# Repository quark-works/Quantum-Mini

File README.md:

# Quantum MINI

rp2040 based controller with a SPDT switch for changing memory bank.

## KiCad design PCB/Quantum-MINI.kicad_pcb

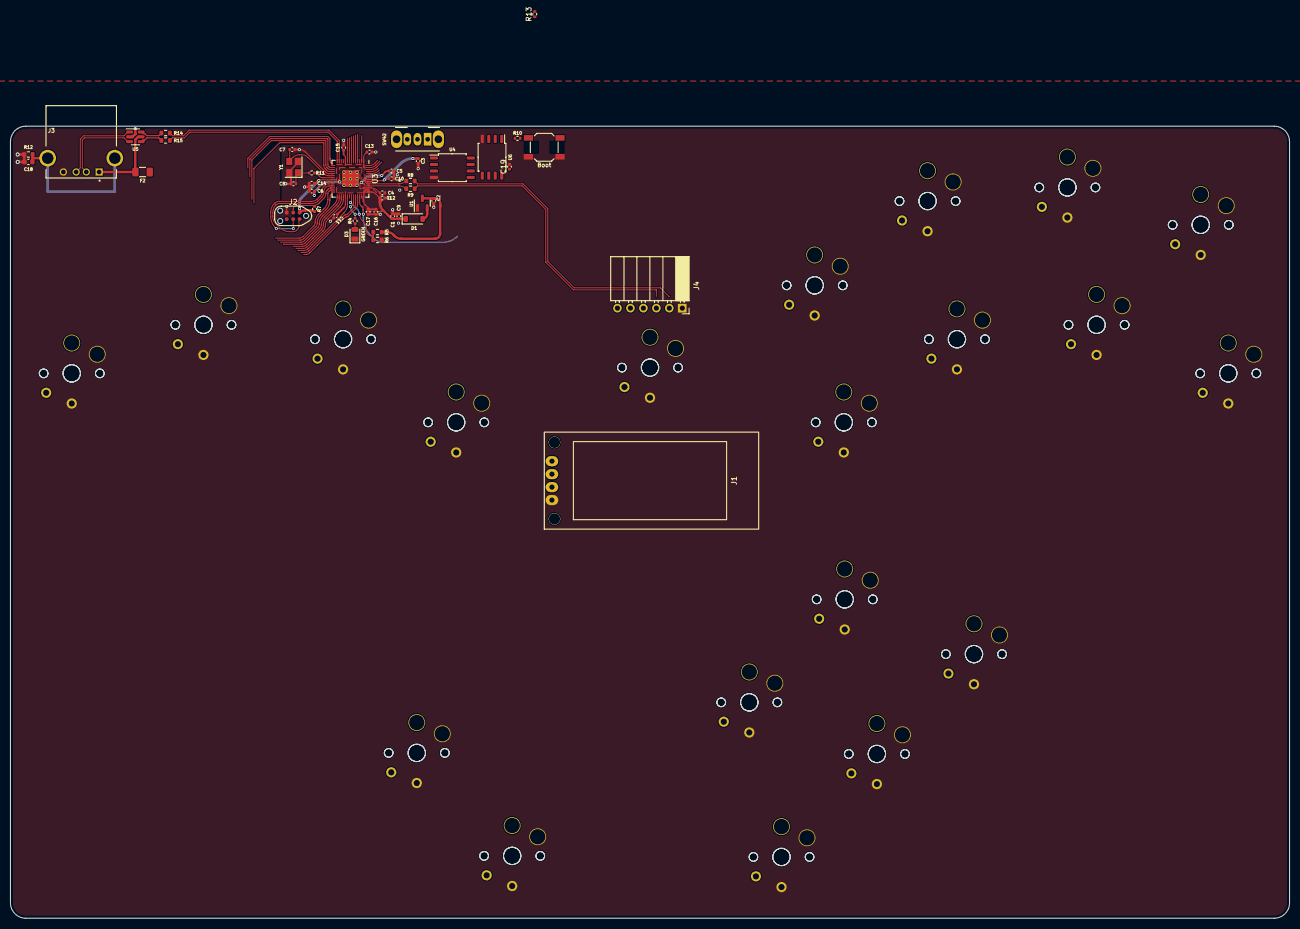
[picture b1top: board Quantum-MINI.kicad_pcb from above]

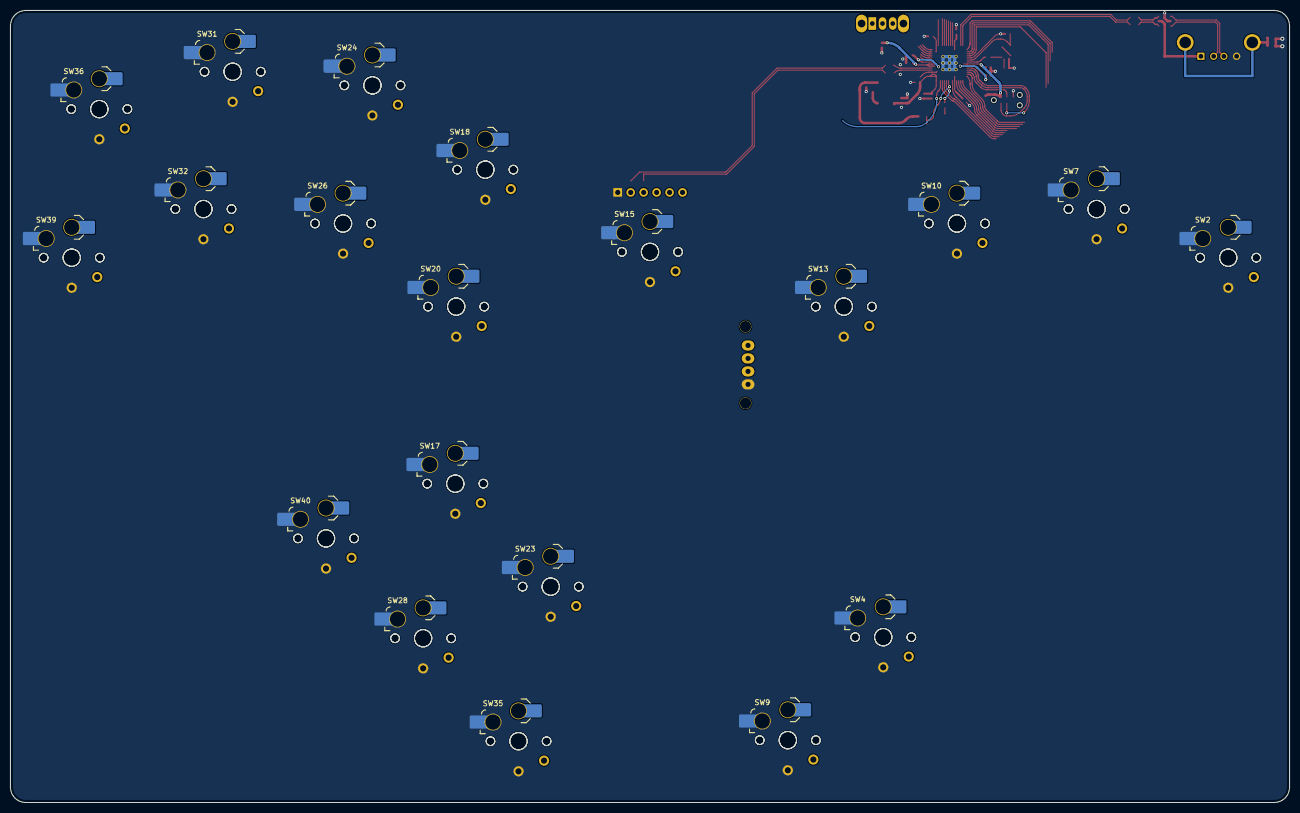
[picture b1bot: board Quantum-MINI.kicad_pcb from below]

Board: 2 copper layers, 250.6 x 155.2 mm, 86 parts (20 on the bottom side), 57 nets.

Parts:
C1, C2, C4, C10: 1uF; C_0402_1005Metric
C3, C5, C6, C11, C12, C13, C14, C15, C16, C17, C19: 100nF; C_0402_1005Metric
C7, C8: 22pF; C_0402_1005Metric
C9: 10uF; C_0402_1005Metric
C18: 4.7uf; C_0603_1608Metric
D1: Schottky Diode; D_SOD-123
D3: GREEN; LED_0805_2012Metric
F2: 500 mA; Fuse_1206_3216Metric
J1: Conn_01x04; SH1107
J2: JTAG_TC2030; CON_TC2030_outlined
J3: USB_A; GCT_USB1130-15-A_REVA
J4: Conn_01x06; PinSocket_1x06_P2.54mm_Horizontal
R4, R7, R10, R13: 10k; R_0402_1005Metric
R5: 5.6k; R_0603_1608Metric
R6: 10k; R_0603_1608Metric
R8, R9: 27; R_0603_1608Metric
R11: 1k; R_0402_1005Metric
R12: 1M; R_0603_1608Metric
R14, R15: 22; R_0603_1608Metric
SW1: Boot; SW_SPST_SKQG_WithStem
SW2, SW4, SW7, SW9, SW10, SW13, SW15, SW17, SW18, SW20, SW23, SW24, SW26, SW28, SW31, SW32, SW35, SW36, SW39, SW40: MX_SW_HS; SW_choc_v1_HS_1u
SW3, SW5, SW6, SW8, SW11, SW12, SW14, SW16, SW19, SW21, SW22, SW25, SW27, SW29, SW30, SW33, SW34, SW37, SW38, SW41: MX_SW_solder; SW_choc_v1_1u
SW42: SW_SPDT; SW_CuK_OS102011MA1QN1_SPDT_Angled
U1: XC6206; SOT-23
U3: RP2040; RP2040-QFN-56
U4, U6: W25Q128JVS; SOIC-8_5.23x5.23mm_P1.27mm
U5: USBLC6-2SC6; SOT-23-6
Y1: 12MHz; Crystal_SMD_3225-4Pin_3.2x2.5mm

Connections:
+1V1: C4.1, C5.1, C6.1, U3.23 (DVDD), U3.45 (VREG_VOUT), U3.50 (DVDD)
+3V3: C1.2, C3.1, C9.1, C10.1, C11.1, C12.1, C13.1, C14.1, C15.1, C16.1, C17.1, C19.1, D1.1 (K), J1.2, J2.1 (VCC), R7.1, R10.2, R13.2, U3.1 (IOVDD), U3.10 (IOVDD), U3.22 (IOVDD), U3.33 (IOVDD), U3.42 (IOVDD), U3.43 (ADC_AVDD), U3.44 (VREG_VIN), U3.48 (USB_VDD), U3.49 (IOVDD), U4.8 (VCC), U6.8 (VCC)
+5V: C2.2, F2.2, J4.4, R5.1, U1.3 (VI)
/D_+: R8.2, U3.47 (D+)
/D_-: R9.2, U3.46 (D-)
/XTAL_O: C8.2, R11.1, Y1.1
A: SW28.2, SW29.1, U3.17 (GPIO14)
B: SW20.2, SW21.1, U3.38 (GPIO26/ADC0)
CS: SW1.2, SW42.2 (B), U3.56 (QSPI_SS_N)
C_DN: SW34.1, SW35.2, U3.18 (GPIO15)
C_LT: SW22.1, SW23.2, U3.16 (GPIO13)
C_RT: SW40.2, SW41.1, U3.27 (GPIO16)
C_UP: SW16.1, SW17.2, U3.15 (GPIO12)
D+: J4.2, R8.1
D-: J4.3, R9.1
DATA: J4.6, U3.40 (GPIO28/ADC2)
DOWN: SW10.2, SW11.1, U3.5 (GPIO3)
GND: C1.1, C2.1, C3.2, C4.2, C5.2, C6.2, C7.1, C8.1, C9.2, C10.2, C11.2, C12.2, C13.2, C14.2, C15.2, C16.2, C17.2, C18.2, C19.2, D3.1 (K), J1.1, J2.5 (GND), J3.4 (GND), J4.1, R6.2, R12.1, SW1.1, SW2.1, SW3.2, SW4.1, SW5.2, SW6.2, SW7.1, SW8.2, SW9.1, SW10.1, SW11.2, SW12.2, SW13.1, SW14.2, SW15.1, SW16.2, SW17.1, SW18.1, SW19.2, SW20.1, SW21.2, SW22.2, SW23.1, SW24.1, SW25.2, SW26.1, SW27.2, SW28.1, SW29.2, SW30.2, SW31.1, SW32.1, SW33.2, SW34.2, SW35.1, SW36.1, SW37.2, SW38.2, SW39.1, SW40.1, SW41.2, U1.1 (GND), U3.19 (TESTEN), U3.57 (GND), U4.4 (GND), U5.2 (GND), U6.4 (GND), Y1.2, Y1.4
L: SW2.2, SW3.1, U3.7 (GPIO5)
LEFT: SW6.1, SW7.2, U3.6 (GPIO4)
LS: SW36.2, SW37.1, U3.31 (GPIO20)
M1: SW4.2, SW5.1, U3.8 (GPIO6)
M2: SW8.1, SW9.2, U3.9 (GPIO7)
MB1: R10.1, SW42.3 (C), U4.1 (~CS)
MB2: R13.1, SW42.1 (A), U6.1 (~CS)
MS: SW30.1, SW31.2, U3.29 (GPIO18)
unnamed: D1.2 (A), U1.2 (VO)
unnamed: D3.2 (A), R4.2
unnamed: C18.1, J3.5 (Shield), R12.2
unnamed: R14.1, U5.6 (I/O1)
unnamed: R15.2, U5.4 (I/O2)
PICO_LED: R4.1, U3.37 (GPIO25)
QSPI_CLK: U3.52 (QSPI_SCLK), U4.6 (CLK), U6.6 (CLK)
R: SW18.2, SW19.1, U3.39 (GPIO27/ADC1)
RIGHT: SW12.1, SW13.2, U3.4 (GPIO2)
SCL: J1.3, U3.12 (GPIO9)
SD0: U3.53 (QSPI_SD0), U4.5 (DI(IO0)), U6.5 (DI(IO0))
SD1: U3.55 (QSPI_SD1), U4.2 (DO(IO1)), U6.2 (DO(IO1))
SD2: U3.54 (QSPI_SD2), U4.3 (IO2), U6.3 (IO2)
SD3: U3.51 (QSPI_SD3), U4.7 (IO3), U6.7 (IO3)
SDA: J1.4, U3.11 (GPIO8)
START: SW14.1, SW15.2, U3.2 (GPIO0)
SWCLK: J2.4 (SWCLK), U3.24 (SWCLK)
SWD: J2.2 (SWDIO), U3.25 (SWDIO)
UP: SW38.1, SW39.2, U3.28 (GPIO17)
USBD+: R14.2, U3.13 (GPIO10)
USBD-: R15.1, U3.14 (GPIO11)
USBDBUS+: J3.3 (D+), U5.1 (I/O1)
USBDBUS-: J3.2 (D-), U5.3 (I/O2)
USBVBUS: F2.1, J3.1 (VBUS), U5.5 (VBUS)
VBUS_SENSE: R5.2, R6.1, U3.36 (GPIO24)
X: SW26.2, SW27.1, U3.32 (GPIO21)
XTAL_IN: C7.2, U3.20 (XTAL_IN), Y1.3
XTAL_OUT: R11.2, U3.21 (XTAL_OUT)
Y: SW24.2, SW25.1, U3.34 (GPIO22)
Z: SW32.2, SW33.1, U3.30 (GPIO19)
~RESET: J2.3 (~RST), R7.2, U3.26 (~RUN)

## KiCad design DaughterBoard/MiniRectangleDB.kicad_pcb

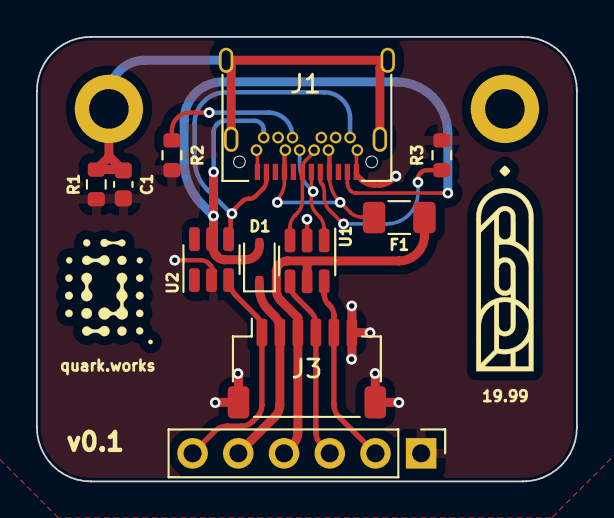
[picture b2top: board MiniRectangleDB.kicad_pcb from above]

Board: 2 copper layers, 30.0 x 24.7 mm, 15 parts (0 on the bottom side), 14 nets.

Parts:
C1: 4.7u; C_0603_1608Metric
D1: Schottky Diode; D_SOD-323
F1: 500 mA; Fuse_1206_3216Metric
H1: MountingHole; MountingHole_2.2mm_M2_DIN965_Pad
H2: MountingHole_Pad; MountingHole_2.2mm_M2_DIN965_Pad
H3: qw logo; qw new logo silk + copper sm
H4: 1999 logo; 1999 logo md
J1: USB C Connector; TYPE-C_24P_QCHT
J2: Conn_01x06; PinHeader_1x06_P2.54mm_Vertical
J3: Conn_01x06; JST_SH_SM06B-SRSS-TB_1x06-1MP_P1.00mm_Horizontal
R1: 1M; R_0603_1608Metric
R2, R3: 5.1k; R_0603_1608Metric
U1, U2: USBLC6-2SC6; SOT-23-6

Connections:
3vCable: D1.2 (A), J1.A2 (TX1+), J1.B2 (TX2+), U2.5 (VBUS)
3vDiode: D1.1 (K), J2.5, J3.2
+5V: F1.2, J2.4, J3.3, U1.5 (VBUS)
D+: J2.2, J3.5, U1.6 (I/O1)
D-: J2.3, J3.4, U1.4 (I/O2)
DATA: J2.6, J3.1, U2.3 (I/O2)
DATABUS: J1.A11 (RX2+), J1.B11 (RX1+), U2.4 (I/O2)
DBUS+: J1.A6 (D+), J1.B6 (D+), U1.1 (I/O1)
DBUS-: J1.A7 (D-), J1.B7 (D-), U1.3 (I/O2)
GND: C1.2, J1.A1 (GND), J1.A12 (GND), J1.B1 (GND), J1.B12 (GND), J2.1, J3.6, R1.1, R2.1, R3.2, U1.2 (GND), U2.2 (GND)
unnamed: F1.1, J1.A4 (VBUS), J1.A9 (VBUS), J1.B4 (VBUS), J1.B9 (VBUS)
unnamed: J1.A5 (CC1), R3.1
unnamed: J1.B5 (CC2), R2.2
unnamed: C1.1, H2.1, J1.S1 (SHIELD), R1.2

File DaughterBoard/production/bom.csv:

Designator,Footprint,Quantity,Value,LCSC Part #
F1,1206,1,500 mA,
H1,MountingHole_2.2mm_M2,1,MountingHole,
H2,MountingHole_2.2mm_M2_DIN965_Pad,1,MountingHole_Pad,
J1,TYPE-C_24P_QCHT,1,USB C Connector,C456013
J2,PinHeader_1x06_P2.54mm_Vertical,1,Conn_01x06,
R1,0603,1,1M,C25190
R2,0603,1,5.1k,C25744
R3,0603,1,5.1k,C25744
"U1, U2",SOT-23-6,2,USBLC6-2SC6,

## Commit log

2026-03-25 Uploaded latest changes
